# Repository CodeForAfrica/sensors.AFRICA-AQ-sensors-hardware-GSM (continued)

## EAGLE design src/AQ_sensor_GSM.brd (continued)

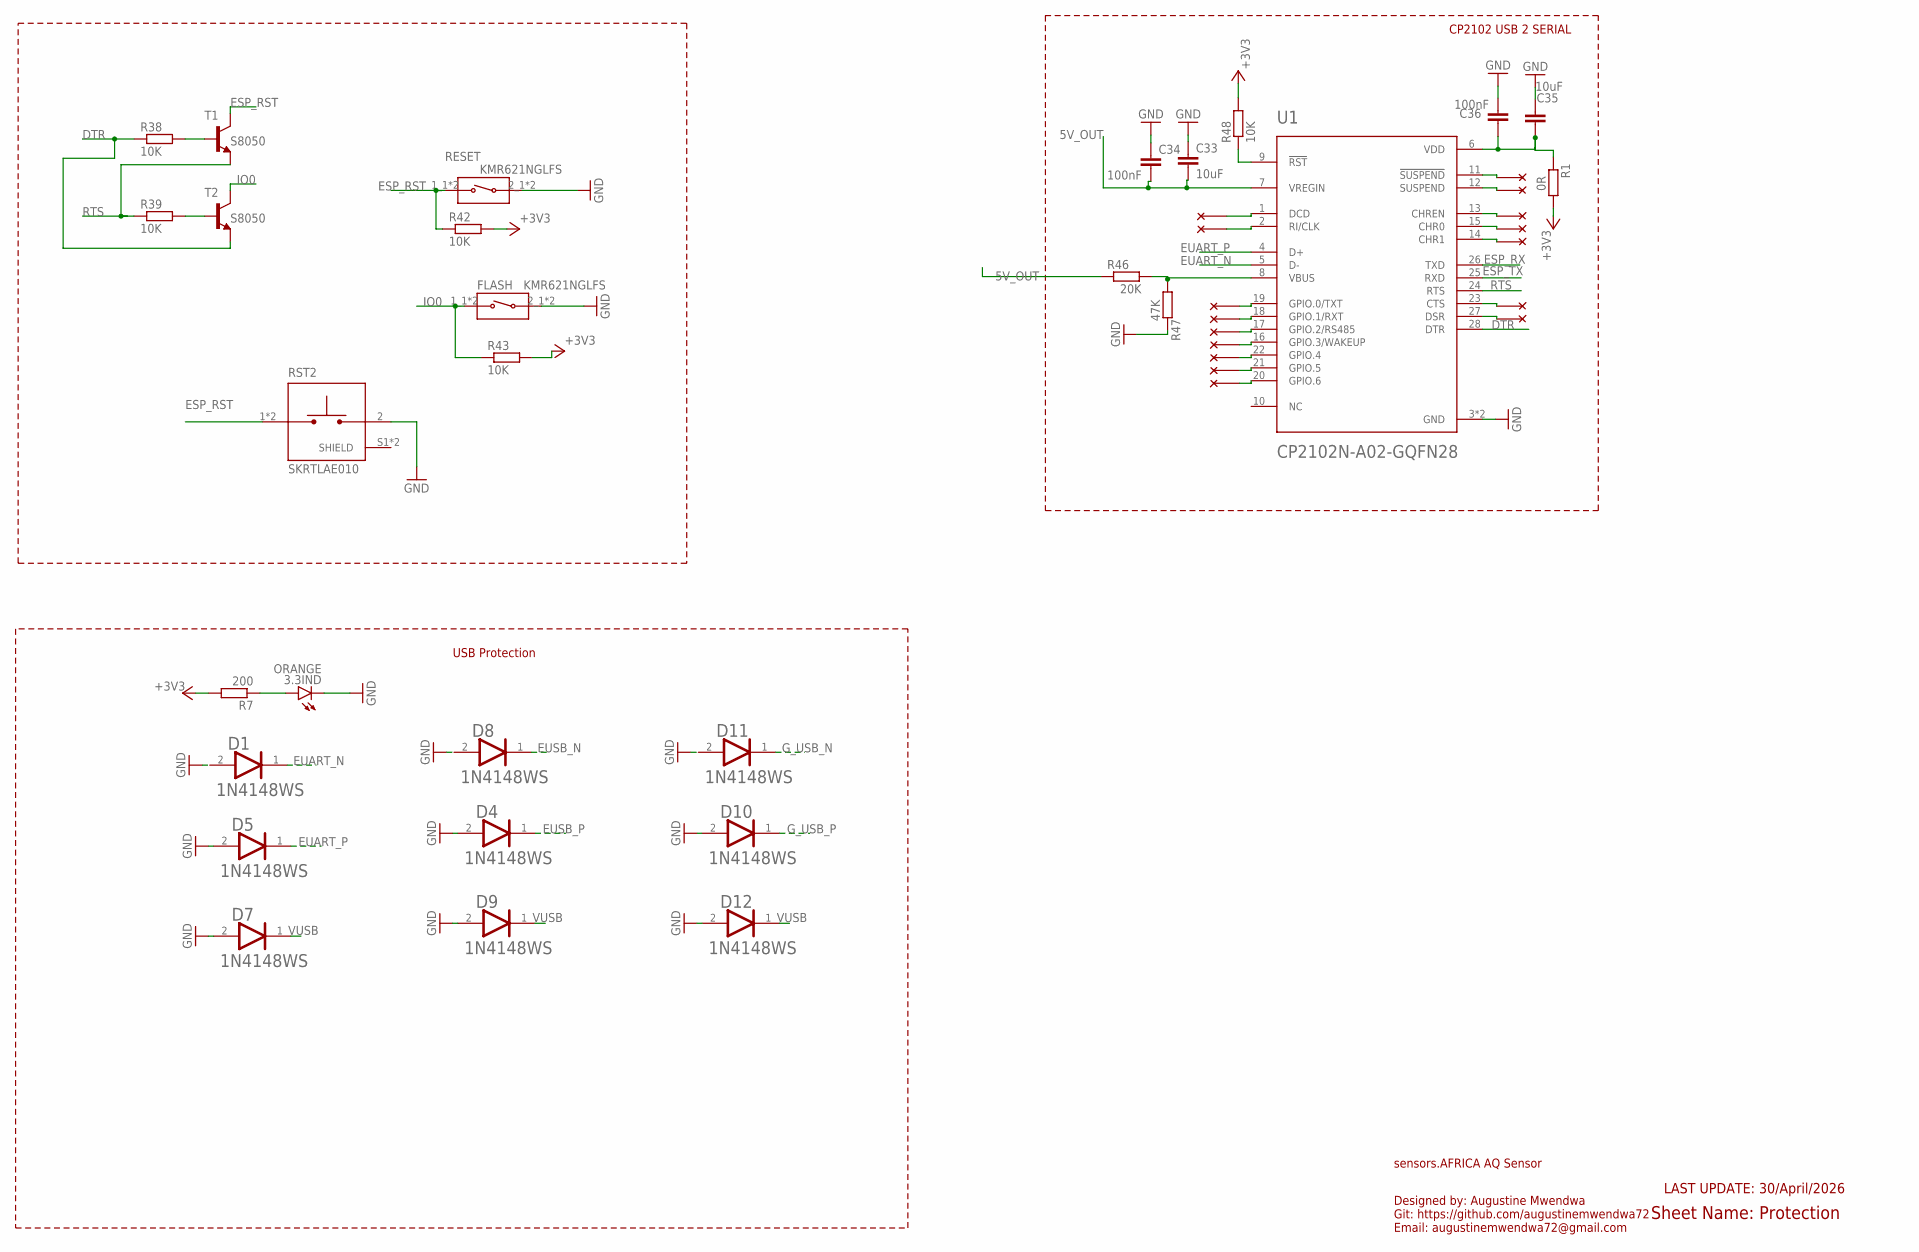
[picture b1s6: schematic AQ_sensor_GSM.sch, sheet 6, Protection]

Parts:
3.3IND: ORANGE; CHIP-LED0603
C33, C35: 10uF; C0603
C34, C36: 100nF; C0805
D1, D4, D5, D7, D8, D9, D10, D11, D12: ON_SEMI_1N4148WSON_SEMI_1N4148WS_0_0; ON_SEMI_1N4148WS_0
FLASH: KMR621NGLFS; SW_KMR621NGLFS
R1: 0R; R0603
R7: 200; R0603
R38, R39, R42, R43, R48: 10K; R0603
R46: 20K; R0603
R47: 47K; R0603
RESET: KMR621NGLFS; SW_KMR621NGLFS
RST2: SKRTLAE010; SW_SKRTLAE010
T1, T2: S8050; SC59-BEC
U1: CP2102N-A02-GQFN28; QFN50P500X500X80-29N

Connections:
5V_OUT: C33.2, C34.2, R46.1, U1.7 (VREGIN); also elsewhere on the board
+3V3: R1.2, R7.2, R42.2, R43.2, R48.2; also elsewhere on the board
DTR: R38.1, T2.E, U1.28 (DTR)
ESP_RST: R42.1, RESET.1_1 (1), RESET.1_2 (1), RST2.1, RST2.3 (1), T1.C; also elsewhere on the board
ESP_RX: U1.26 (TXD); also elsewhere on the board
ESP_TX: U1.25 (RXD); also elsewhere on the board
EUART_N: D1.1 (CATHODE), U1.5 (D-); also elsewhere on the board
EUART_P: D5.1 (CATHODE), U1.4 (D+); also elsewhere on the board
EUSB_N: D8.1 (CATHODE); also elsewhere on the board
EUSB_P: D4.1 (CATHODE); also elsewhere on the board
GND: 3.3IND.C, C33.1, C34.1, C35.1, C36.1, D1.2 (ANODE), D4.2 (ANODE), D5.2 (ANODE), D7.2 (ANODE), D8.2 (ANODE), D9.2 (ANODE), D10.2 (ANODE), D11.2 (ANODE), D12.2 (ANODE), FLASH.2_1 (2), FLASH.2_2 (2), R47.2, RESET.2_1 (2), RESET.2_2 (2), RST2.2, U1.3 (GND), U1.29 (GND); also elsewhere on the board
G_USB_N: D11.1 (CATHODE); also elsewhere on the board
G_USB_P: D10.1 (CATHODE); also elsewhere on the board
IO0: FLASH.1_1 (1), FLASH.1_2 (1), R43.1, T2.C; also elsewhere on the board
unnamed: 3.3IND.A, R7.1
unnamed: R38.2, T1.B
unnamed: R39.2, T2.B
unnamed: R48.1, U1.9 (!RST)
unnamed: R46.2, R47.1, U1.8 (VBUS)
unnamed: C35.2, C36.2, R1.1, U1.6 (VDD)
RTS: R39.1, T1.E, U1.24 (RTS)
VUSB: D7.1 (CATHODE), D9.1 (CATHODE), D12.1 (CATHODE); also elsewhere on the board

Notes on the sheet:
CP2102 USB 2 SERIAL
USB Protection
sensors.AFRICA AQ Sensor
Sheet Name: Protection
Designed by: Augustine Mwendwa Git: https://github.com/augustinemwendwa72 Email: augustinemwendwa72@gmail.com
LAST UPDATE: 30/April/2026

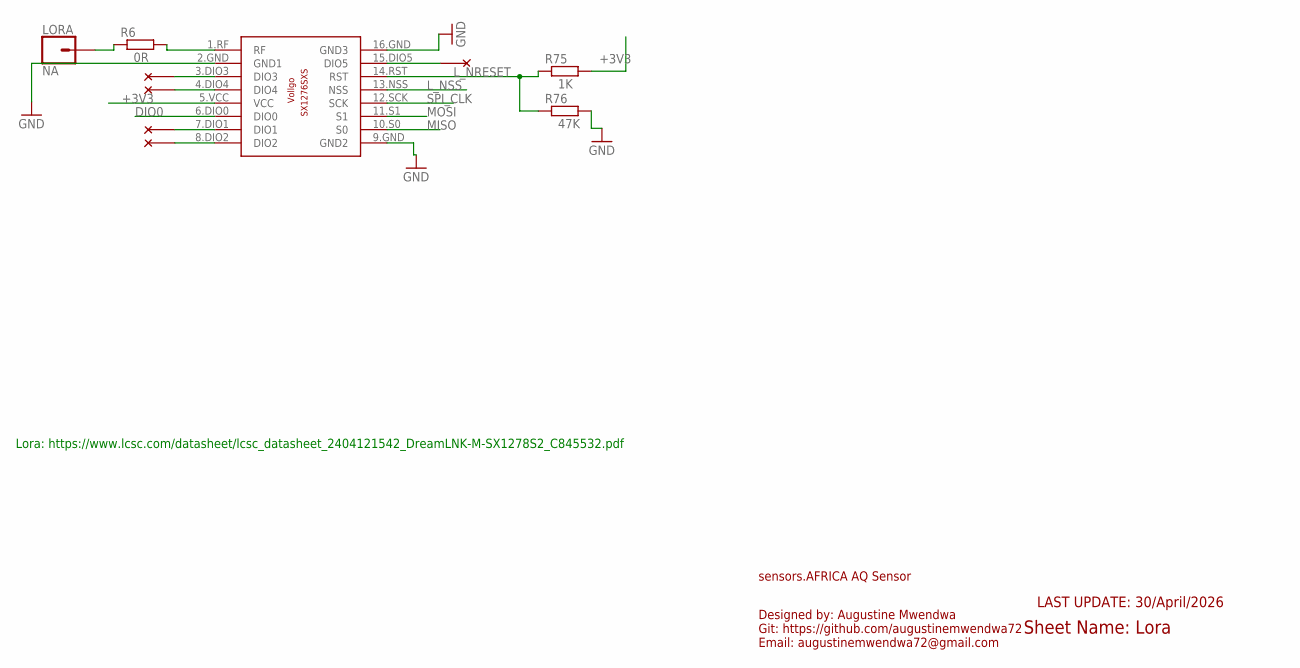
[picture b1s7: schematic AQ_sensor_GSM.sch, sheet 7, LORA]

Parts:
LORA: NA; 1X01
R6: 0R; R0603
R75: 1K; R0603
R76: 47K; R0603
U$86: SX1276SXS

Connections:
+3V3: R75.2, U$86.5.VCC (VCC); also elsewhere on the board
DIO0: U$86.6.DIO0 (DIO0); also elsewhere on the board
GND: R76.2, U$86.2.GND (GND1), U$86.9.GND (GND2), U$86.16.GND (GND3); also elsewhere on the board
L_NRESET: R75.1, R76.1, U$86.14.RST (RST); also elsewhere on the board
L_NSS: U$86.13.NSS (NSS); also elsewhere on the board
MISO: U$86.10.S0 (S0); also elsewhere on the board
MOSI: U$86.11.S1 (S1); also elsewhere on the board
unnamed: LORA.1, R6.1
unnamed: R6.2, U$86.1.RF (RF)
SPI_CLK: U$86.12.SCK (SCK); also elsewhere on the board

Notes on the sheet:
Lora: https://www.lcsc.com/datasheet/lcsc_datasheet_2404121542_DreamLNK-M-SX1278S2_C845532.pdf
sensors.AFRICA AQ Sensor
Sheet Name: Lora
Designed by: Augustine Mwendwa Git: https://github.com/augustinemwendwa72 Email: augustinemwendwa72@gmail.com
LAST UPDATE: 30/April/2026

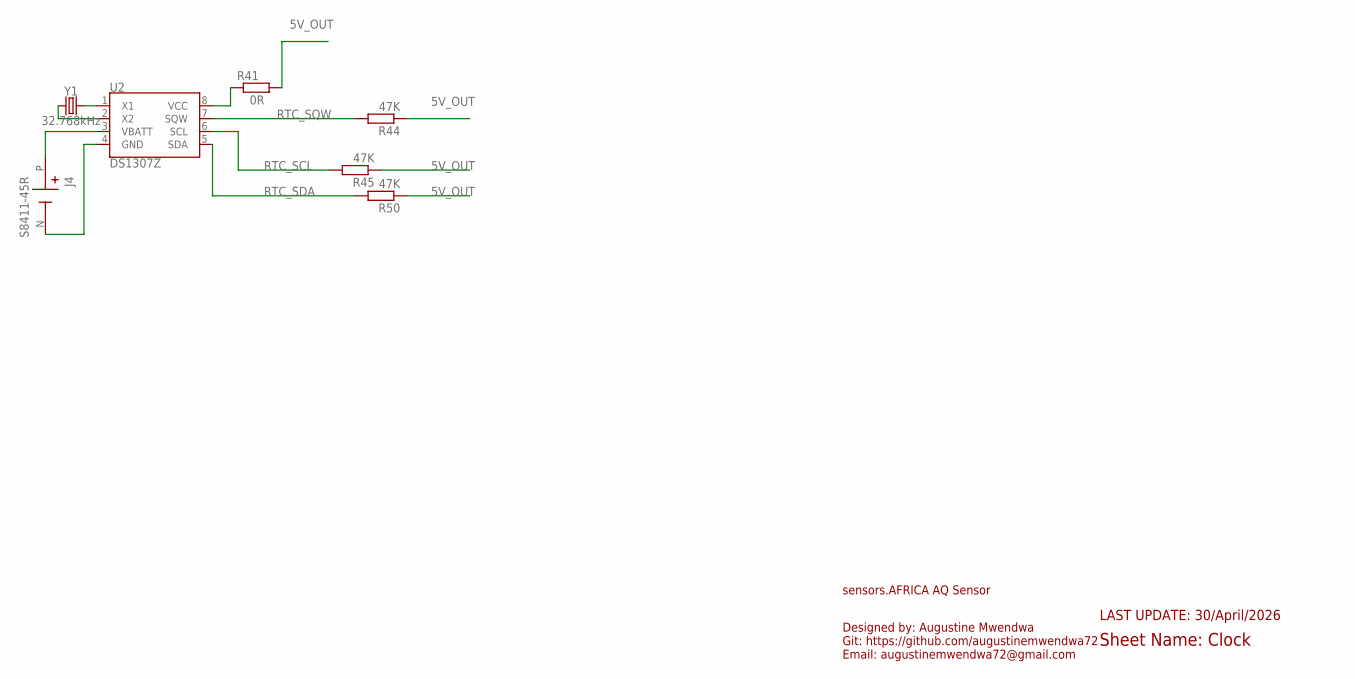
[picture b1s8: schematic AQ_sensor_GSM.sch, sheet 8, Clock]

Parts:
J4: S8411-45R; HARWIN_S8411-45R
R41: 0R; R0603
R44, R45, R50: 47K; R0603
U2: DS1307Z; SO08-0.15
Y1: 32.768kHz; CRYSTAL-SMD-3.2X1.5MM

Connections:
5V_OUT: R41.2, R44.1, R45.1, R50.1; also elsewhere on the board
unnamed: U2.1 (X1), Y1.P$2 (2)
unnamed: U2.2 (X2), Y1.P$1 (1)
unnamed: J4.P (+), U2.3 (VBATT)
unnamed: J4.N (-), U2.4 (GND)
unnamed: R41.1, U2.8 (VCC)
RTC_SCL: R45.2, U2.6 (SCL); also elsewhere on the board
RTC_SDA: R50.2, U2.5 (SDA); also elsewhere on the board
RTC_SQW: R44.2, U2.7 (SQW); also elsewhere on the board

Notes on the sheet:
sensors.AFRICA AQ Sensor
Sheet Name: Clock
Designed by: Augustine Mwendwa Git: https://github.com/augustinemwendwa72 Email: augustinemwendwa72@gmail.com
LAST UPDATE: 30/April/2026

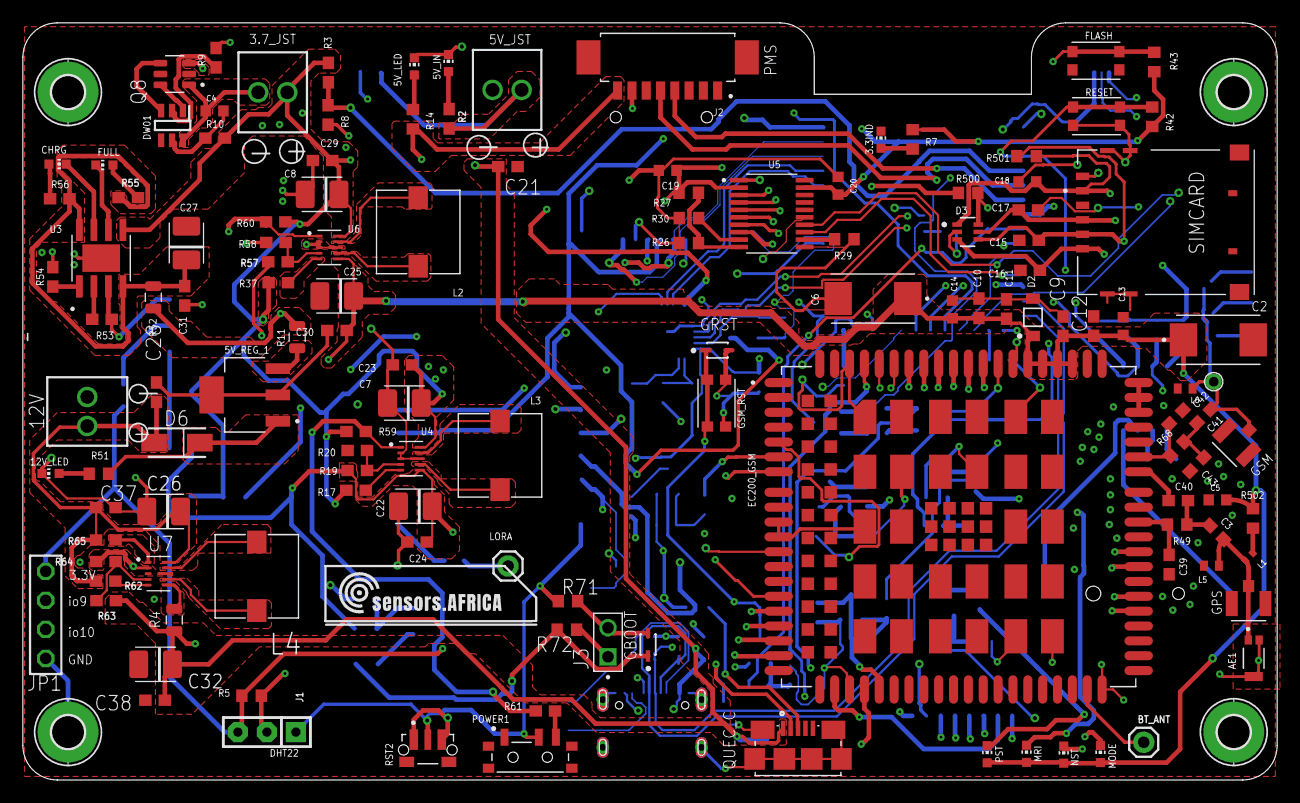
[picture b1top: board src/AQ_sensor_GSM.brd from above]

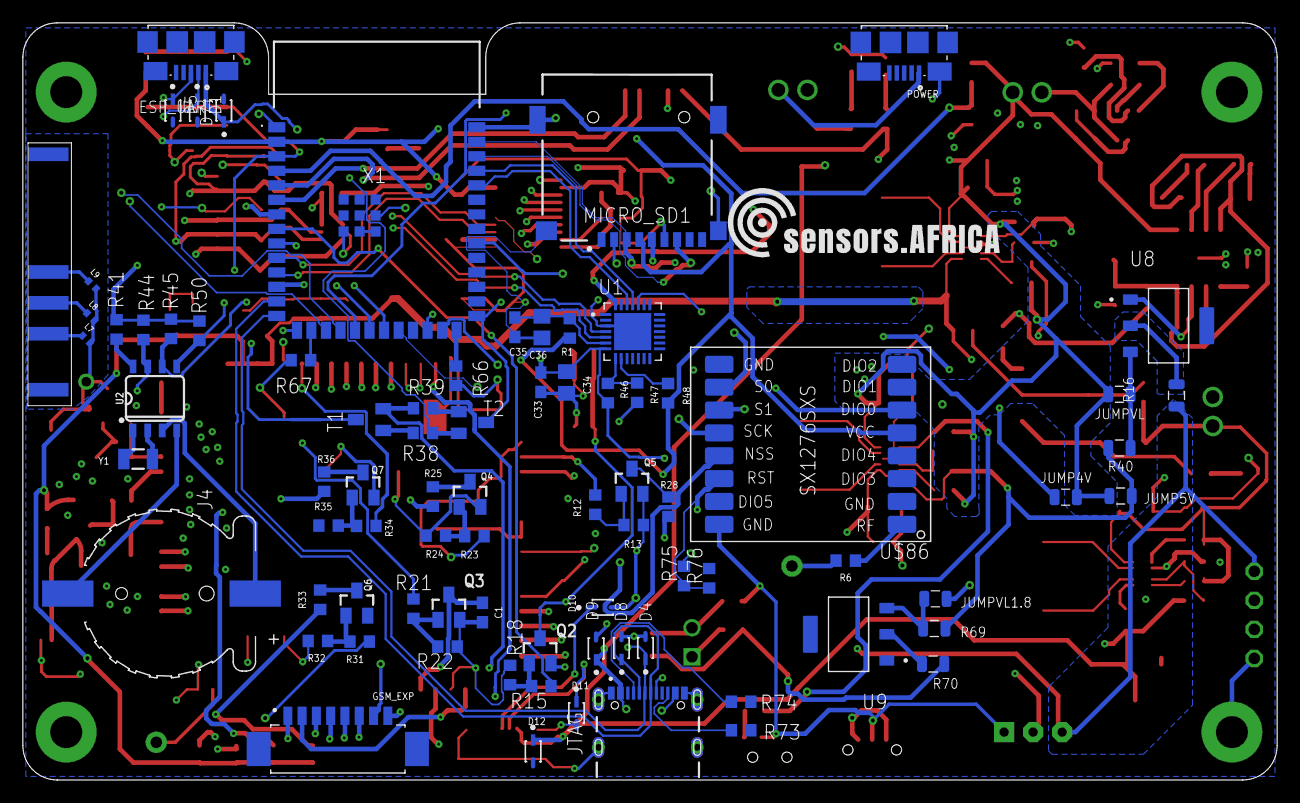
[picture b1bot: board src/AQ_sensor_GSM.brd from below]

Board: 4 copper layers, 109.8 x 66.2 mm, 214 parts (80 on the bottom side), 149 nets.

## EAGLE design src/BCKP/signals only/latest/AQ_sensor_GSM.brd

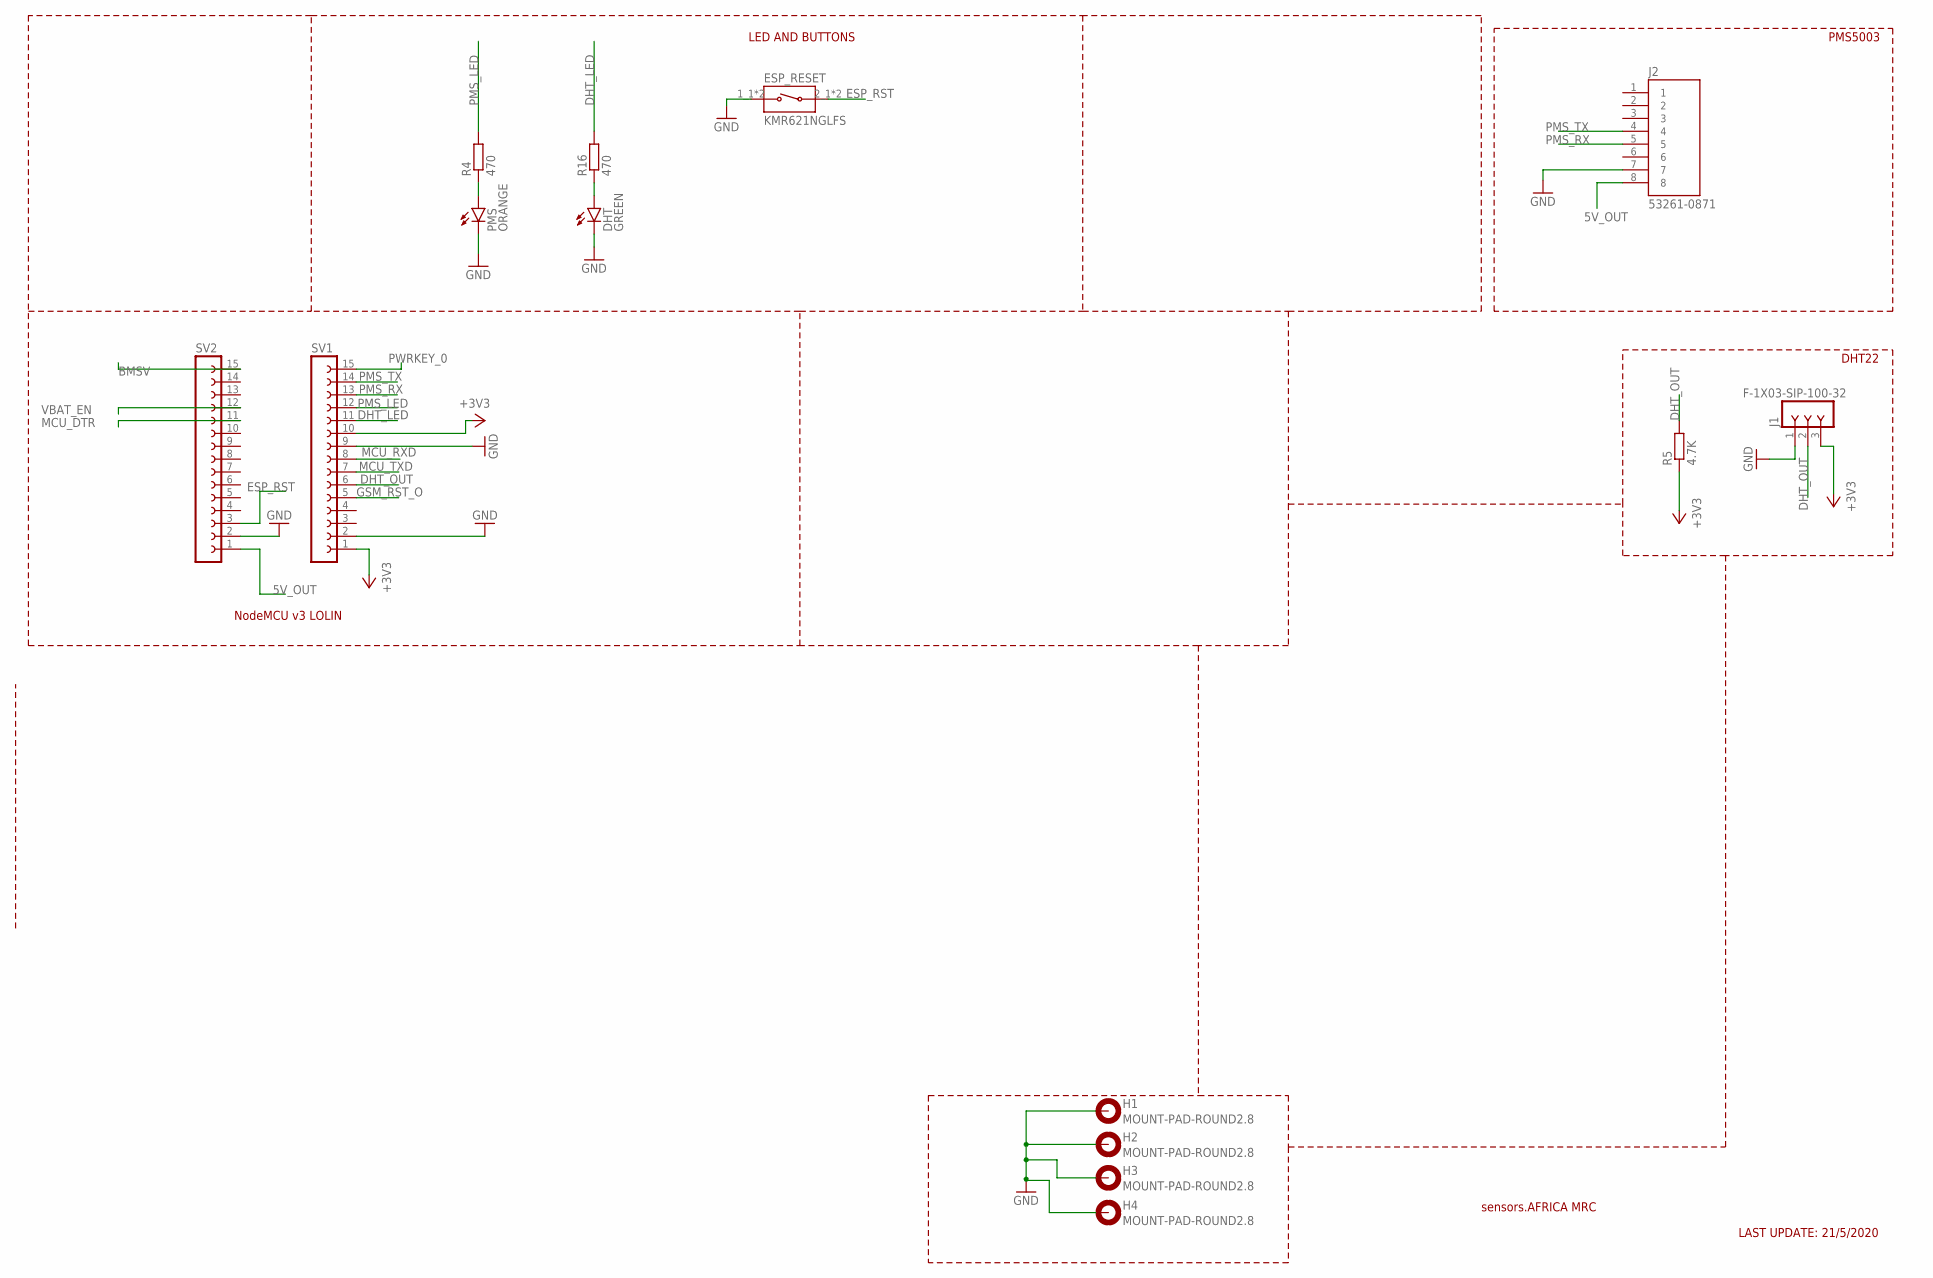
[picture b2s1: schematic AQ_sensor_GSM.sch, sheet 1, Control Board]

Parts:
DHT: GREEN; CHIP-LED0603
ESP_RESET: KMR621NGLFS; SW_KMR621NGLFS
H1, H2, H3, H4: MOUNT-PAD-ROUND2.8; 2,8-PAD
J1: F-1X03-SIP-100-32; SIP-100-03-32
J2: 53261-0871; MOLEX_53261-0871
PMS: ORANGE; CHIP-LED0603
R4, R16: 470; R0603
R5: 4.7K; R0603
SV1, SV2: FE15-1; FE15

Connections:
5V_OUT: J2.8, SV2.1; also elsewhere on the board
+3V3: J1.3, R5.1, SV1.1, SV1.10; also elsewhere on the board
BMSV: SV2.15; also elsewhere on the board
DHT_LED: R16.2, SV1.11
DHT_OUT: J1.2, R5.2, SV1.6
ESP_RST: ESP_RESET.2_1 (2), ESP_RESET.2_2 (2), SV2.3
GND: DHT.C, ESP_RESET.1_1 (1), ESP_RESET.1_2 (1), H1.B2,8, H2.B2,8, H3.B2,8, H4.B2,8, J1.1, J2.7, PMS.C, SV1.2, SV1.9, SV2.2; also elsewhere on the board
GSM_RST_O: SV1.5; also elsewhere on the board
MCU_DTR: SV2.11; also elsewhere on the board
MCU_RXD: SV1.8; also elsewhere on the board
MCU_TXD: SV1.7; also elsewhere on the board
unnamed: PMS.A, R4.1
unnamed: DHT.A, R16.1
PMS_LED: R4.2, SV1.12
PMS_RX: J2.5, SV1.13
PMS_TX: J2.4, SV1.14
PWRKEY_0: SV1.15; also elsewhere on the board
VBAT_EN: SV2.12

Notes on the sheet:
sensors.AFRICA MRC
LAST UPDATE: 21/5/2020
LED AND BUTTONS
PMS5003
DHT22
NodeMCU v3 LOLIN

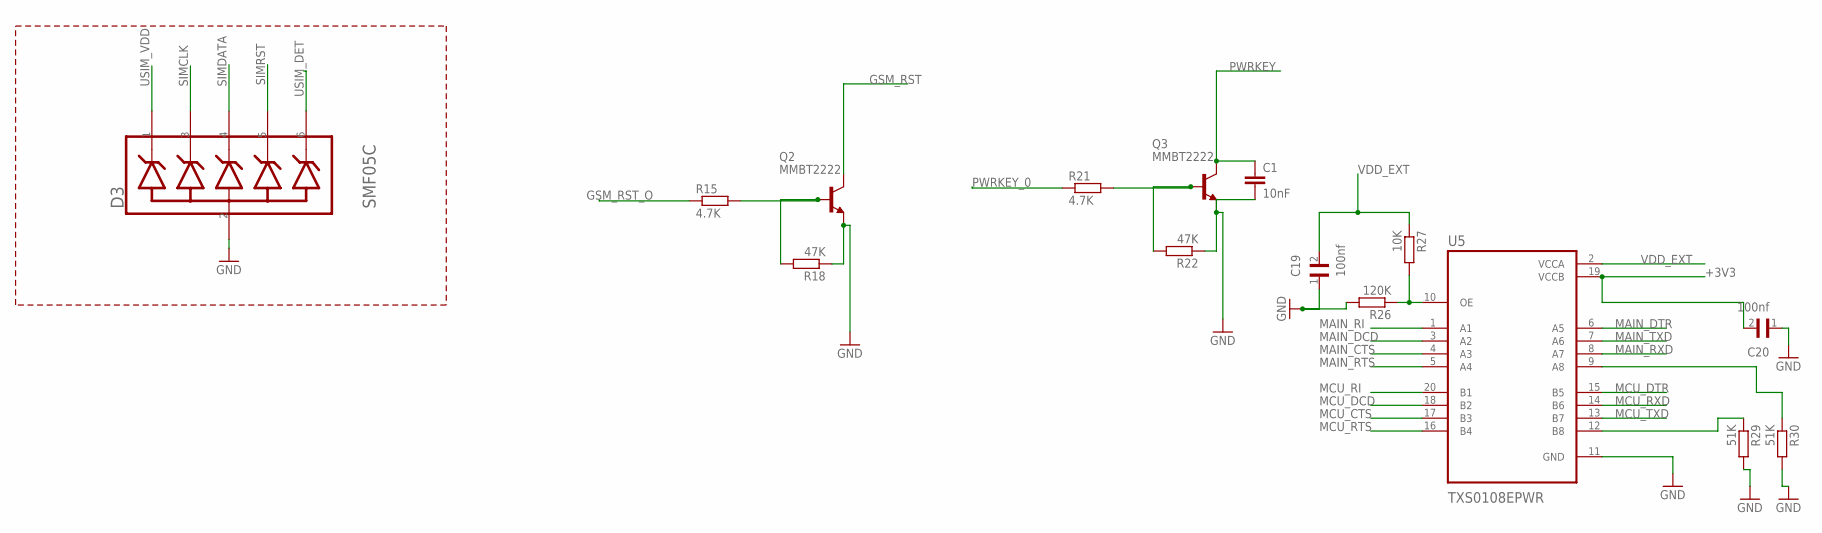
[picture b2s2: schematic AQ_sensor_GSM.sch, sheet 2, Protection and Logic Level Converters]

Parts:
C1: 10nF; 0603
C19, C20: 100nf; CAPC1608X90N
D3: SEMTECH_SMF05CSEMTECH_SMF05C_0_0; SEMTECH_SMF05C_0
Q2, Q3: MMBT2222; SOT23-BEC
R15, R21: 4.7K; R0603
R18, R22: 47K; R0603
R26: 120K; R0603
R27: 10K; R0603
R29, R30: 51K; R0603
U5: TXS0108EPWR; SOP65P640X120-20N

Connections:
+3V3: C20.2, U5.19 (VCCB); also elsewhere on the board
GND: C1.2, C19.1, C20.1, D3.2 (ANODE), Q2.E, Q3.E, R18.1, R22.1, R26.2, R29.2, R30.2, U5.11 (GND); also elsewhere on the board
GSM_RST: Q2.C; also elsewhere on the board
GSM_RST_O: R15.1; also elsewhere on the board
MAIN_CTS: U5.4 (A3); also elsewhere on the board
MAIN_DCD: U5.3 (A2); also elsewhere on the board
MAIN_DTR: U5.6 (A5); also elsewhere on the board
MAIN_RI: U5.1 (A1); also elsewhere on the board
MAIN_RTS: U5.5 (A4); also elsewhere on the board
MAIN_RXD: U5.8 (A7); also elsewhere on the board
MAIN_TXD: U5.7 (A6); also elsewhere on the board
MCU_CTS: U5.17 (B3)
MCU_DCD: U5.18 (B2)
MCU_DTR: U5.15 (B5); also elsewhere on the board
MCU_RI: U5.20 (B1)
MCU_RTS: U5.16 (B4)
MCU_RXD: U5.14 (B6); also elsewhere on the board
MCU_TXD: U5.13 (B7); also elsewhere on the board
unnamed: Q2.B, R15.2, R18.2
unnamed: Q3.B, R21.2, R22.2
unnamed: R26.1, R27.2, U5.10 (OE)
unnamed: R30.1, U5.9 (A8)
unnamed: R29.1, U5.12 (B8)
PWRKEY: C1.1, Q3.C; also elsewhere on the board
PWRKEY_0: R21.1; also elsewhere on the board
SIMCLK: D3.3 (2_CATHODE); also elsewhere on the board
SIMDATA: D3.4 (3_CATHODE); also elsewhere on the board
SIMRST: D3.5 (4_CATHODE); also elsewhere on the board
USIM_DET: D3.6 (5_CATHODE); also elsewhere on the board
USIM_VDD: D3.1 (1_CATHODE); also elsewhere on the board
VDD_EXT: C19.2, R27.1, U5.2 (VCCA); also elsewhere on the board

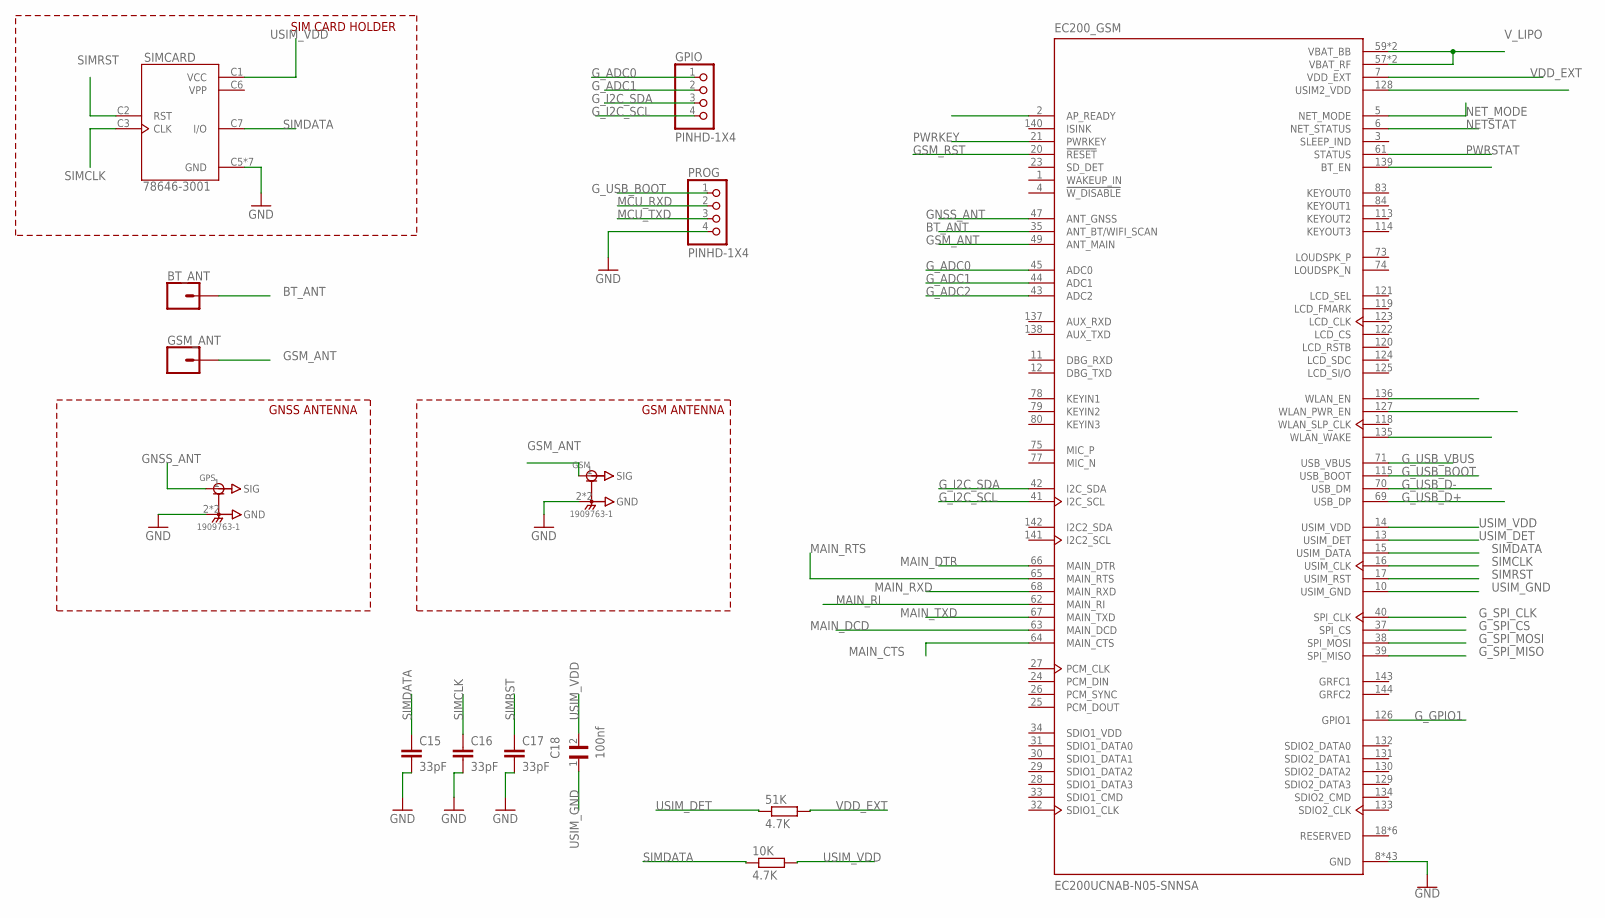
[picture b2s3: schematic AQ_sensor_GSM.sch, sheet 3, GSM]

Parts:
10K, 51K: 4.7K; R0603
BT_ANT: CONN_01; 1X01
C15, C16, C17: 33pF; C0603
C18: 100nf; CAPC1608X90N
EC200_GSM: EC200UCNAB-N05-SNNSA; XCVR_EC200UCNAB-N05-SNNSA
GPIO: PINHD-1X4; 1X04
GPS: 1909763-1; TE_1909763-1
GSM: 1909763-1; TE_1909763-1
GSM_ANT: CONN_01; 1X01
PROG: PINHD-1X4; 1X04
SIMCARD: 78646-3001; MOLEX_78646-3001

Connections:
BT_ANT: BT_ANT.1, EC200_GSM.35 (ANT_BT/WIFI_SCAN)
GND: C15.2, C16.2, C17.2, EC200_GSM.8 (GND), EC200_GSM.9 (GND), EC200_GSM.19 (GND), EC200_GSM.22 (GND), EC200_GSM.36 (GND), EC200_GSM.46 (GND), EC200_GSM.48 (GND), EC200_GSM.50 (GND), EC200_GSM.51 (GND), EC200_GSM.52 (GND), EC200_GSM.53 (GND), EC200_GSM.54 (GND), EC200_GSM.56 (GND), EC200_GSM.72 (GND), EC200_GSM.76 (GND), EC200_GSM.85 (GND), EC200_GSM.86 (GND), EC200_GSM.87 (GND), EC200_GSM.88 (GND), EC200_GSM.89 (GND), EC200_GSM.90 (GND), EC200_GSM.91 (GND), EC200_GSM.92 (GND), EC200_GSM.93 (GND), EC200_GSM.94 (GND), EC200_GSM.95 (GND), EC200_GSM.96 (GND), EC200_GSM.97 (GND), EC200_GSM.98 (GND), EC200_GSM.99 (GND), EC200_GSM.100 (GND), EC200_GSM.101 (GND), EC200_GSM.102 (GND), EC200_GSM.103 (GND), EC200_GSM.104 (GND), EC200_GSM.105 (GND), EC200_GSM.106 (GND), EC200_GSM.107 (GND), EC200_GSM.108 (GND), EC200_GSM.109 (GND), EC200_GSM.110 (GND), EC200_GSM.111 (GND), EC200_GSM.112 (GND), GPS.2 (GND), GPS.3 (GND), GSM.2 (GND), GSM.3 (GND), PROG.4, SIMCARD.C5 (GND), SIMCARD.G1 (GND), SIMCARD.G2 (GND), SIMCARD.G3 (GND), SIMCARD.G4 (GND), SIMCARD.G5 (GND), SIMCARD.G6 (GND); also elsewhere on the board
GNSS_ANT: EC200_GSM.47 (ANT_GNSS), GPS.1 (SIG)
GSM_ANT: EC200_GSM.49 (ANT_MAIN), GSM.1 (SIG), GSM_ANT.1
GSM_RST: EC200_GSM.20 (!RESET); also elsewhere on the board
G_ADC0: EC200_GSM.45 (ADC0), GPIO.1
G_ADC1: EC200_GSM.44 (ADC1), GPIO.2
G_ADC2: EC200_GSM.43 (ADC2)
G_GPIO1: EC200_GSM.126 (GPIO1)
G_I2C_SCL: EC200_GSM.41 (I2C_SCL), GPIO.4
G_I2C_SDA: EC200_GSM.42 (I2C_SDA), GPIO.3
G_SPI_CLK: EC200_GSM.40 (SPI_CLK)
G_SPI_CS: EC200_GSM.37 (SPI_CS)
G_SPI_MISO: EC200_GSM.39 (SPI_MISO)
G_SPI_MOSI: EC200_GSM.38 (SPI_MOSI)
G_USB_BOOT: EC200_GSM.115 (USB_BOOT), PROG.1
G_USB_D+: EC200_GSM.69 (USB_DP); also elsewhere on the board
G_USB_D-: EC200_GSM.70 (USB_DM); also elsewhere on the board
G_USB_VBUS: EC200_GSM.71 (USB_VBUS)
MAIN_CTS: EC200_GSM.64 (MAIN_CTS); also elsewhere on the board
MAIN_DCD: EC200_GSM.63 (MAIN_DCD); also elsewhere on the board
MAIN_DTR: EC200_GSM.66 (MAIN_DTR); also elsewhere on the board
MAIN_RI: EC200_GSM.62 (MAIN_RI); also elsewhere on the board
MAIN_RTS: EC200_GSM.65 (MAIN_RTS); also elsewhere on the board
MAIN_RXD: EC200_GSM.68 (MAIN_RXD); also elsewhere on the board
MAIN_TXD: EC200_GSM.67 (MAIN_TXD); also elsewhere on the board
MCU_RXD: PROG.2; also elsewhere on the board
MCU_TXD: PROG.3; also elsewhere on the board
NETSTAT: EC200_GSM.6 (NET_STATUS); also elsewhere on the board
NET_MODE: EC200_GSM.5 (NET_MODE); also elsewhere on the board
PWRKEY: EC200_GSM.21 (PWRKEY); also elsewhere on the board
PWRSTAT: EC200_GSM.61 (STATUS); also elsewhere on the board
SDIO1_VDD: EC200_GSM.34 (SDIO1_VDD)
SIMCLK: C16.1, EC200_GSM.16 (USIM_CLK), SIMCARD.C3 (CLK); also elsewhere on the board
SIMDATA: 10K.1, C15.1, EC200_GSM.15 (USIM_DATA), SIMCARD.C7 (I/O); also elsewhere on the board
SIMRST: C17.1, EC200_GSM.17 (USIM_RST), SIMCARD.C2 (RST); also elsewhere on the board
USIM_DET: 51K.1, EC200_GSM.13 (USIM_DET); also elsewhere on the board
USIM_GND: C18.1, EC200_GSM.10 (USIM_GND)
USIM_VDD: 10K.2, C18.2, EC200_GSM.14 (USIM_VDD), SIMCARD.C1 (VCC); also elsewhere on the board
VDD_EXT: 51K.2, EC200_GSM.7 (VDD_EXT); also elsewhere on the board
VPP: SIMCARD.C6 (VPP)
V_LIPO: EC200_GSM.57 (VBAT_RF), EC200_GSM.58 (VBAT_RF), EC200_GSM.59 (VBAT_BB), EC200_GSM.60 (VBAT_BB); also elsewhere on the board

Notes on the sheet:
SIM CARD HOLDER
GSM ANTENNA
GNSS ANTENNA

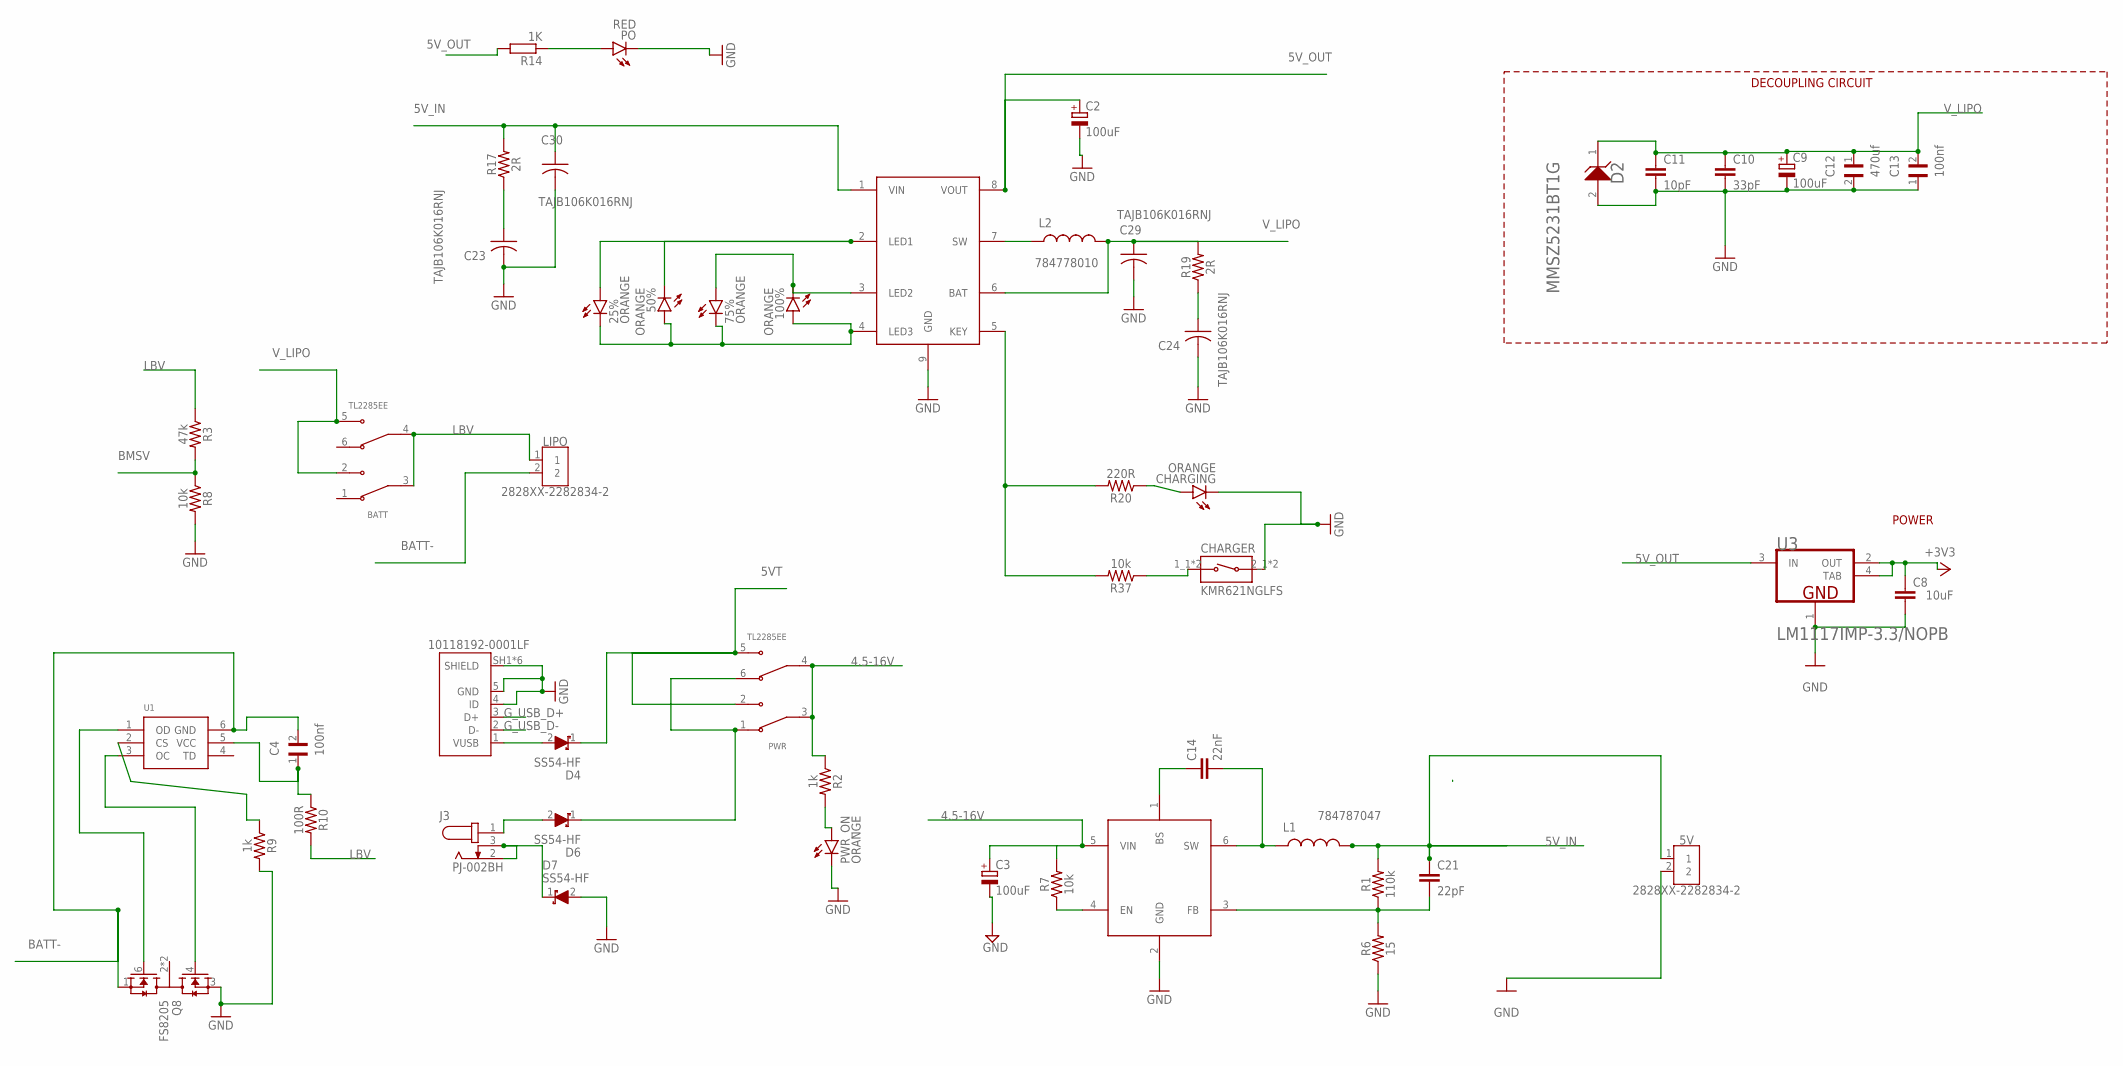
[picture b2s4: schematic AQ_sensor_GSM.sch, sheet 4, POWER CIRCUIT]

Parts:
5V: 2828XX-2282834-2; TERMBLK_254-2N
25%, 50%, 75%, 100%: ORANGE; CHIP-LED0603
BATT: TL2285EE; SW_TL2285EE
C2, C3, C9: 100uF; PANASONIC_D
C4, C13: 100nf; CAPC1608X90N
C8: 10uF; C0603
C10: 33pF; C0603
C11: 10pF; C0603
C12: 470uf; CAPMP7343X430N
C14: 22nF; 0402-TIGHT
C21: 22pF; 0402-TIGHT
C23, C24, C29, C30: TAJB106K016RNJ; CAP_TANT_B
CHARGER: KMR621NGLFS; SW_KMR621NGLFS
CHARGING: ORANGE; CHIP-LED0603
D2: ON_SEMICONDUCTOR_MMSZ5231BT1GON_SEMICONDUCTOR_MMS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; ON_SEMICONDUCTOR_MMSZ5231BT1G_0
D4, D6, D7: SS54-HF; DIOM5025X220N
J3: PJ-002BH; CUI_PJ-002BH
L1: 784787047
L2: 784778010
LIPO: 2828XX-2282834-2; TERMBLK_254-2N
MT2492: MT2492; SOT95P280X145-6N
PB_IN: 10118192-0001LF; AMPHENOL_10118192-0001LF
PO: RED; CHIP-LED0603
PWR: TL2285EE; SW_TL2285EE
PWR_ON: ORANGE; CHIP-LED0603
Q8: FS8205; SOT95P280X145-6N
R1: 110k; 0603
R2, R9: 1k; 0603
R3: 47k; 0603
R6: 15; 0603
R7, R8, R37: 10k; 0603
R10: 100R; 0603
R14: 1K; R0603
R17, R19: 2R; 0603
R20: 220R; 0603
U1: DW01-P; SOT23-6L
U3: TEXAS_INSTRUMENTS_LM1117IMP-3.3-NOPBTEXAS_INSTRUM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; TEXAS_INSTRUMENTS_LM1117IMP-3.3-NOPB_0
U$2: IP5306IP5306; SOIC127P600X165-9T209N

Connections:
4.5-16V: C3.+, MT2492.5 (VIN), PWR.3 (COM1), PWR.4 (COM2), R2.1, R7.2
5VT: D4.1 (K), PWR.2 (NO1), PWR.5 (NO2)
5V_IN: 5V.1, C21.1, C30.1, L1.2, R1.2, R17.2, U$2.1 (VIN)
5V_OUT: C2.+, R14.2, U3.3 (IN), U$2.8 (VOUT); also elsewhere on the board
+3V3: C8.1, U3.2 (OUT), U3.4 (TAB); also elsewhere on the board
BATT-: C4.2, LIPO.2, Q8.1 (S1), U1.6 (GND)
BMSV: R3.2, R8.1; also elsewhere on the board
GND: 5V.2, C2.-, C3.-, C8.2, C9.-, C10.2, C11.2, C12.2, C13.1, C23.2, C24.2, C29.2, C30.2, CHARGER.2_1 (2), CHARGER.2_2 (2), CHARGING.C, D2.2 (A), D7.2 (A), MT2492.2 (GND), PB_IN.4 (ID), PB_IN.5 (GND), PB_IN.SH1 (SHIELD), PB_IN.SH2 (SHIELD), PB_IN.SH3 (SHIELD), PB_IN.SH4 (SHIELD), PB_IN.SH5 (SHIELD), PB_IN.SH6 (SHIELD), PO.C, PWR_ON.C, Q8.3 (S2), R6.1, R8.2, R9.2, U3.1 (GND), U$2.9 (GND); also elsewhere on the board
G_USB_D+: PB_IN.3 (D+); also elsewhere on the board
G_USB_D-: PB_IN.2 (D-); also elsewhere on the board
LBV: BATT.3 (COM1), BATT.4 (COM2), LIPO.1, R3.1, R10.2
unnamed: C14.1, MT2492.1 (BS)
unnamed: C14.2, L1.1, MT2492.6 (SW)
unnamed: Q8.6 (G1), U1.1 (OD)
unnamed: C21.2, MT2492.3 (FB), R1.1, R6.2
unnamed: MT2492.4 (EN), R7.1
unnamed: C23.1, R17.1
unnamed: 25%.C, 50%.A, 75%.C, 100%.A, U$2.4 (LED3)
unnamed: 25%.A, 50%.C, U$2.2 (LED1)
unnamed: 75%.A, 100%.C, U$2.3 (LED2)
unnamed: Q8.4 (G2), U1.3 (OC)
unnamed: CHARGER.1_1 (1), CHARGER.1_2 (1), R37.1
unnamed: L2.1, U$2.7 (SW)
unnamed: C24.1, R19.1
unnamed: PO.A, R14.1
unnamed: PWR_ON.A, R2.2
unnamed: C4.1, R10.1, U1.5 (VCC)
unnamed: R20.2, R37.2, U$2.5 (KEY)
unnamed: CHARGING.A, R20.1
unnamed: R9.1, U1.2 (CS)
unnamed: D4.2 (A), PB_IN.1 (VUSB)
unnamed: D7.1 (K), J3.2, J3.3
unnamed: D6.2 (A), J3.1
VUSB: D6.1 (K), PWR.1 (NC1), PWR.6 (NC2)
V_LIPO: BATT.2 (NO1), BATT.5 (NO2), C9.+, C10.1, C11.1, C12.1, C13.2, C29.1, D2.1 (K), L2.2, R19.2, U$2.6 (BAT); also elsewhere on the board

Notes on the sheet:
DECOUPLING CIRCUIT
POWER
